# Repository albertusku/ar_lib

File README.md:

# AR_LIB

Not all the soft is tested and the 99% of the libs I have made are dependent of other libs so you must need to check if you have the other libs

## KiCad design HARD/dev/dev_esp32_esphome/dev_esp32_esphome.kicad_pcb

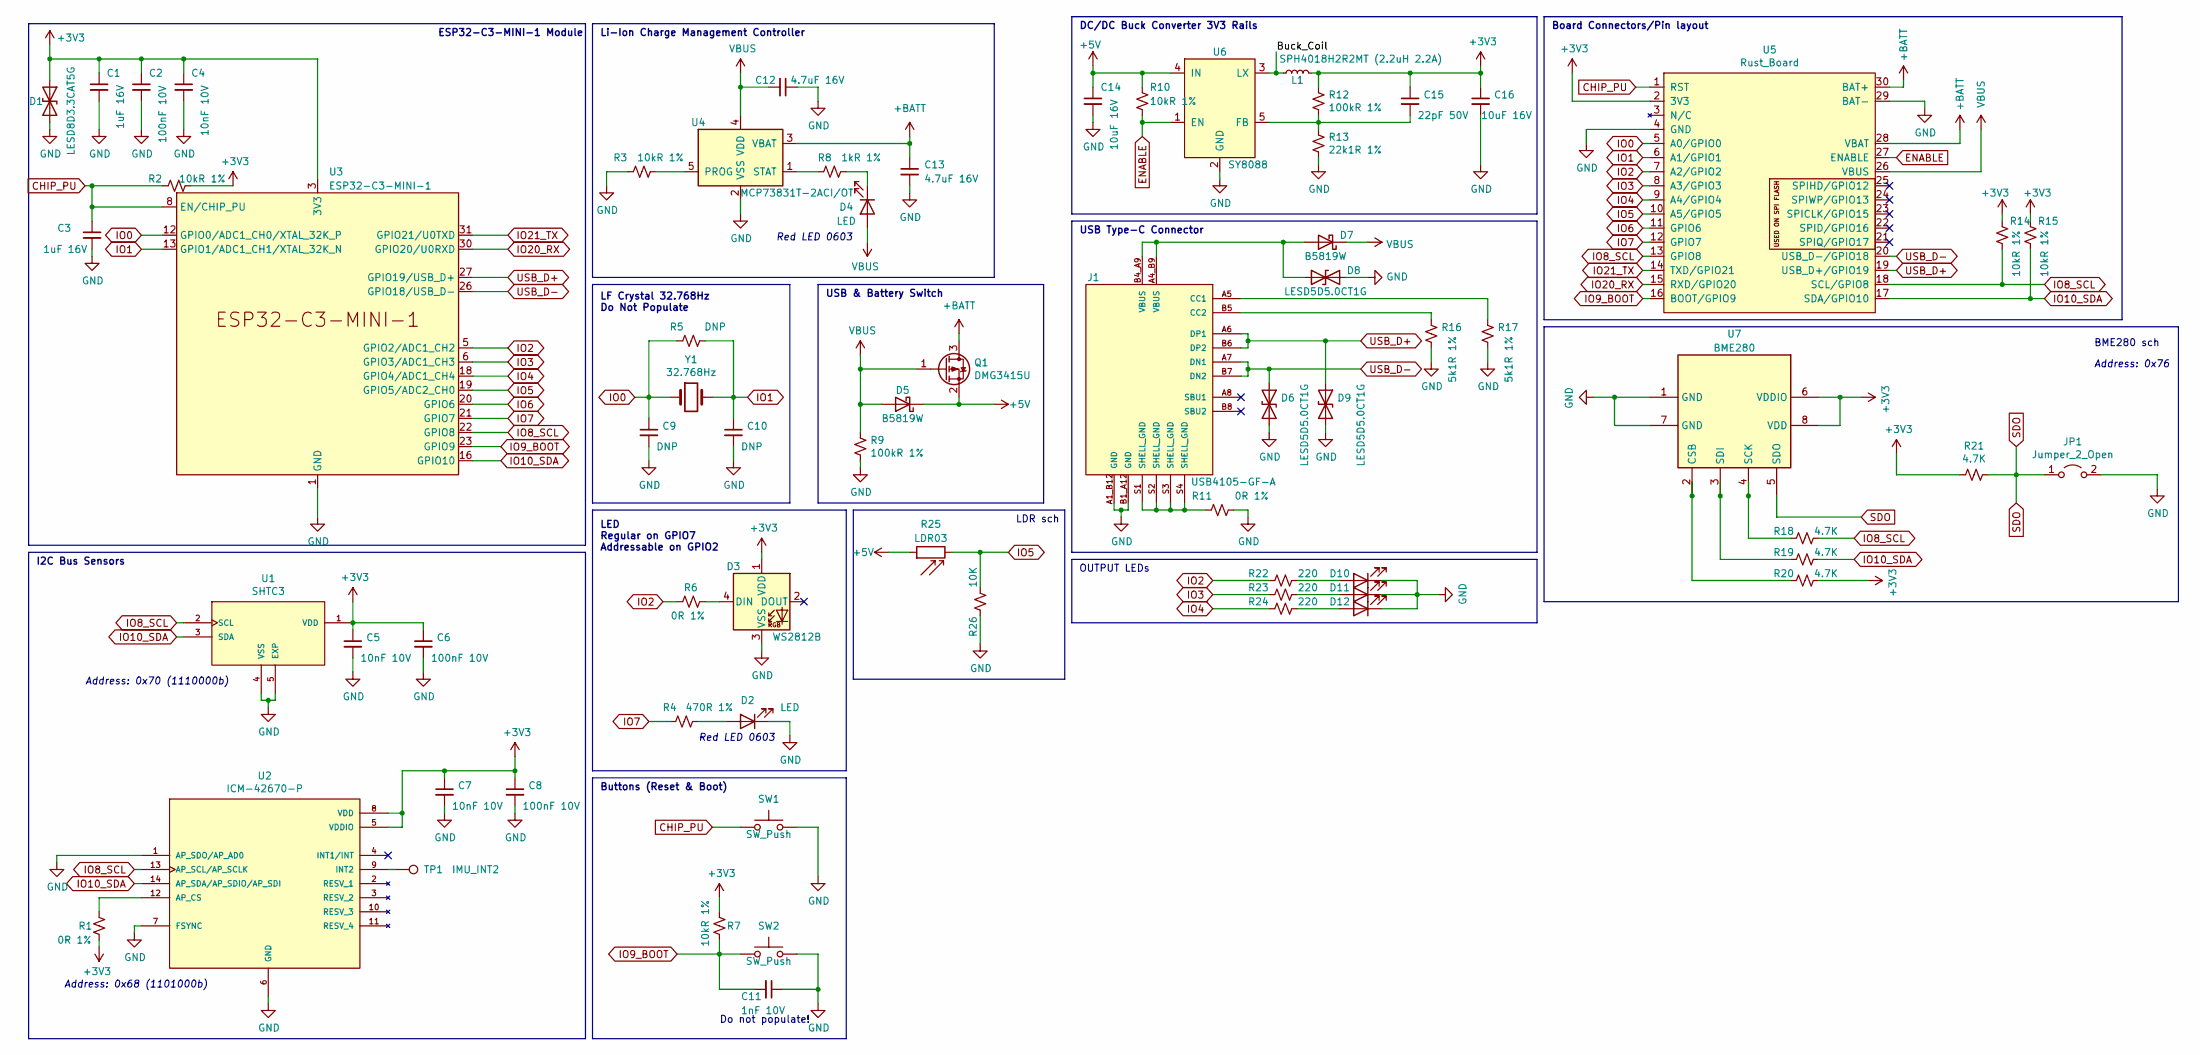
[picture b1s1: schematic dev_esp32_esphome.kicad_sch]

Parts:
C1, C3: 1uF 16V; C_0402_1005Metric; LCSC C52923
C2, C6, C8: 100nF 10V; C_0402_1005Metric; LCSC C1525
C4, C5, C7: 10nF 10V; C_0402_1005Metric; LCSC C15195
C9, C10: DNP; C_0402_1005Metric
C11: 1nF 10V; C_0402_1005Metric; LCSC C1523
C12, C13: 4.7uF 16V; C_0603_1608Metric; LCSC C19666
C14, C16: 10uF 16V; C_0805_2012Metric; LCSC C15850
C15: 22pF 50V; C_0603_1608Metric; LCSC C1653
D1: LESD8D3.3CAT5G; SOD-882; LCSC C172409
D2, D4, D10, D11, D12: LED; LED_0603_1608Metric; LCSC C2286
D3: WS2812B; LED_SK6812MINI_PLCC4_3.5x3.5mm_P1.75mm; LCSC C527089
D5, D7: B5819W; D_SOD-123; LCSC C8598
D6, D8, D9: LESD5D5.0CT1G; D_SOD-523; LCSC C383211
J1: USB4105-GF-A; GCT_USB4105-GF-A; PARTREV A3; LCSC C165948
JP1: Jumper_2_Open; SolderJumper-2_P1.3mm_Open_TrianglePad1.0x1.5mm
L1: SPH4018H2R2MT (2.2uH 2.2A); L_Bourns-SRN4018; LCSC C370436
Q1: DMG3415U; SOT-23; LCSC C96616
R1, R6, R11: 0R 1%; R_0402_1005Metric; LCSC C17168
R2, R3, R7, R10, R14, R15: 10kR 1%; R_0402_1005Metric; LCSC C25744
R4: 470R 1%; R_0402_1005Metric; LCSC C25117
R5: DNP; R_0402_1005Metric
R8: 1kR 1%; R_0402_1005Metric; LCSC C11702
R9, R12: 100kR 1%; R_0402_1005Metric; LCSC C25741
R13: 22k1R 1%; R_0402_1005Metric; LCSC C43473
R16, R17: 5k1R 1%; R_0402_1005Metric; LCSC C25905
R18, R19, R20, R21: 4.7K; R_0805_2012Metric
R22, R23, R24: 220; R_0402_1005Metric; LCSC C17168
R25: LDR03; R_LDR_10x8.5mm_P7.6mm_Vertical
R26: 10K; R_0402_1005Metric; LCSC C25117
SW1, SW2: SW_Push; SW_SPST_PTS810; LCSC C116501
TP1: IMU_INT2; TestPoint_Pad_D1.0mm
U1: SHTC3; SON100P200X200X80-5N; PARTREV 3; LCSC C194656
U2: ICM-42670-P; IC_ICM-42670-P; PARTREV 1.0
U3: ESP32-C3-MINI-1
U4: MCP73831T-2ACI/OT; SOT-23-5; LCSC C424093
U5: Rust_Board
U6: SY8088; SOT-23-5; LCSC C479072
U7: BME280; Bosch_LGA-8_2.5x2.5mm_P0.65mm_ClockwisePinNumbering
Y1: 32.768Hz; Crystal_SMD_3215-2Pin_3.2x1.5mm

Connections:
+3V3: C1.1, C2.1, C4.1, C5.1, C6.1, C7.1, C8.1, C15.1, C16.1, D1.1 (A1), D3.1 (VDD), L1.2, R1.2, R2.2, R7.1, R12.1, R14.1, R15.1, R20.1, R21.2, U1.1 (VDD), U2.5 (VDDIO), U2.8 (VDD), U3.3 (3V3), U5.2 (3V3), U7.6 (VDDIO), U7.8 (VDD)
+5V: C14.1, D5.1 (K), Q1.2 (S), R10.1, R25.1, U6.4 (IN)
+BATT: C13.1, Q1.3 (D), U4.3 (VBAT), U5.28 (VBAT), U5.30 (BAT+)
/Buck_Coil: L1.1, U6.3 (LX)
CHIP_PU: C3.1, R2.1, SW1.1, U3.8 (EN/CHIP_PU), U5.1 (RST)
ENABLE: R10.2, U5.27 (ENABLE), U6.1 (EN)
GND: C1.2, C2.2, C3.2, C4.2, C5.2, C6.2, C7.2, C8.2, C9.2, C10.2, C11.1, C12.1, C13.2, C14.2, C16.2, D1.2 (A2), D2.1 (K), D3.3 (VSS), D6.2 (A2), D8.2 (A2), D9.2 (A2), D10.1 (K), D11.1 (K), D12.1 (K), J1.A1_B12 (GND), J1.B1_A12 (GND), JP1.2 (B), R3.1, R9.2, R11.2, R13.2, R16.2, R17.2, R26.1, SW1.2, SW2.2, U1.4 (VSS), U1.5 (EXP), U2.1 (AP_SDO/AP_AD0), U2.6 (GND), U2.7 (FSYNC), U3.1 (GND), U3.2 (GND), U3.11 (GND), U3.14 (GND), U3.36 (GND), U3.37 (GND), U3.38 (GND), U3.39 (GND), U3.40 (GND), U3.41 (GND), U3.42 (GND), U3.43 (GND), U3.44 (GND), U3.45 (GND), U3.46 (GND), U3.47 (GND), U3.48 (GND), U3.49 (GND), U3.50 (GND), U3.51 (GND), U3.52 (GND), U3.53 (GND), U4.2 (VSS), U5.4 (GND), U5.29 (BAT-), U6.2 (GND), U7.1 (GND), U7.7 (GND)
IO0: C9.1, R5.1, U3.12 (GPIO0/ADC1_CH0/XTAL_32K_P), U5.5 (A0/GPIO0), Y1.1
IO1: C10.1, R5.2, U3.13 (GPIO1/ADC1_CH1/XTAL_32K_N), U5.6 (A1/GPIO1), Y1.2
IO2: R6.1, R22.1, U3.5 (GPIO2/ADC1_CH2), U5.7 (A2/GPIO2)
IO3: R23.1, U3.6 (GPIO3/ADC1_CH3), U5.8 (A3/GPIO3)
IO4: R24.1, U3.18 (GPIO4/ADC1_CH4), U5.9 (A4/GPIO4)
IO5: R25.2, R26.2, U3.19 (GPIO5/ADC2_CH0), U5.10 (A5/GPIO5)
IO6: U3.20 (GPIO6), U5.11 (GPIO6)
IO7: R4.1, U3.21 (GPIO7), U5.12 (GPIO7)
IO8_SCL: R14.2, R18.1, U1.2 (SCL), U2.13 (AP_SCL/AP_SCLK), U3.22 (GPIO8), U5.13 (GPIO8), U5.18 (SCL/GPIO8)
IO9_BOOT: C11.2, R7.2, SW2.1, U3.23 (GPIO9), U5.16 (BOOT/GPIO9)
IO10_SDA: R15.2, R19.1, U1.3 (SDA), U2.14 (AP_SDA/AP_SDIO/AP_SDI), U3.16 (GPIO10), U5.17 (SDA/GPIO10)
IO20_RX: U3.30 (GPIO20/U0RXD), U5.15 (RXD/GPIO20)
IO21_TX: U3.31 (GPIO21/U0TXD), U5.14 (TXD/GPIO21)
unnamed: D2.2 (A), R4.2
unnamed: D3.4 (DIN), R6.2
unnamed: D4.1 (K), R8.2
unnamed: D7.2 (A), D8.1 (A1), J1.A4_B9 (VBUS), J1.B4_A9 (VBUS)
unnamed: D10.2 (A), R22.2
unnamed: D11.2 (A), R23.2
unnamed: D12.2 (A), R24.2
unnamed: J1.A5 (CC1), R17.1
unnamed: J1.B5 (CC2), R16.1
unnamed: J1.S1 (SHELL_GND), J1.S2 (SHELL_GND), J1.S3 (SHELL_GND), J1.S4 (SHELL_GND), R11.1
unnamed: R1.1, U2.12 (AP_CS)
unnamed: TP1.1, U2.9 (INT2)
unnamed: R3.2, U4.5 (PROG)
unnamed: R8.1, U4.1 (STAT)
unnamed: C15.2, R12.2, R13.1, U6.5 (FB)
unnamed: R20.2, U7.2 (CSB)
unnamed: R18.2, U7.4 (SCK)
unnamed: R19.2, U7.3 (SDI)
SDO: JP1.1 (A), R21.1, U7.5 (SDO)
USB_D+: D9.1 (A1), J1.A6 (DP1), J1.B6 (DP2), U3.27 (GPIO19/USB_D+), U5.19 (USB_D+/GPIO19)
USB_D-: D6.1 (A1), J1.A7 (DN1), J1.B7 (DN2), U3.26 (GPIO18/USB_D-), U5.20 (USB_D-/GPIO18)
VBUS: C12.2, D4.2 (A), D5.2 (A), D7.1 (K), Q1.1 (G), R9.1, U4.4 (VDD), U5.26 (VBUS)

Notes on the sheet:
Board Connectors/Pin layout
BME280 sch
Address: 0x68 (1101000b)
OUTPUT LEDs
I2C Bus Sensors
LED Regular on GPIO7 Addressable on GPIO2
Red LED 0603
LDR sch
Buttons (Reset & Boot)
USB & Battery Switch
LF Crystal 32.768Hz Do Not Populate
USB Type-C Connector
Address: 0x76
Li-Ion Charge Management Controller
DC/DC Buck Converter 3V3 Rails
ESP32-C3-MINI-1 Module
Do not populate!
Address: 0x70 (1110000b)

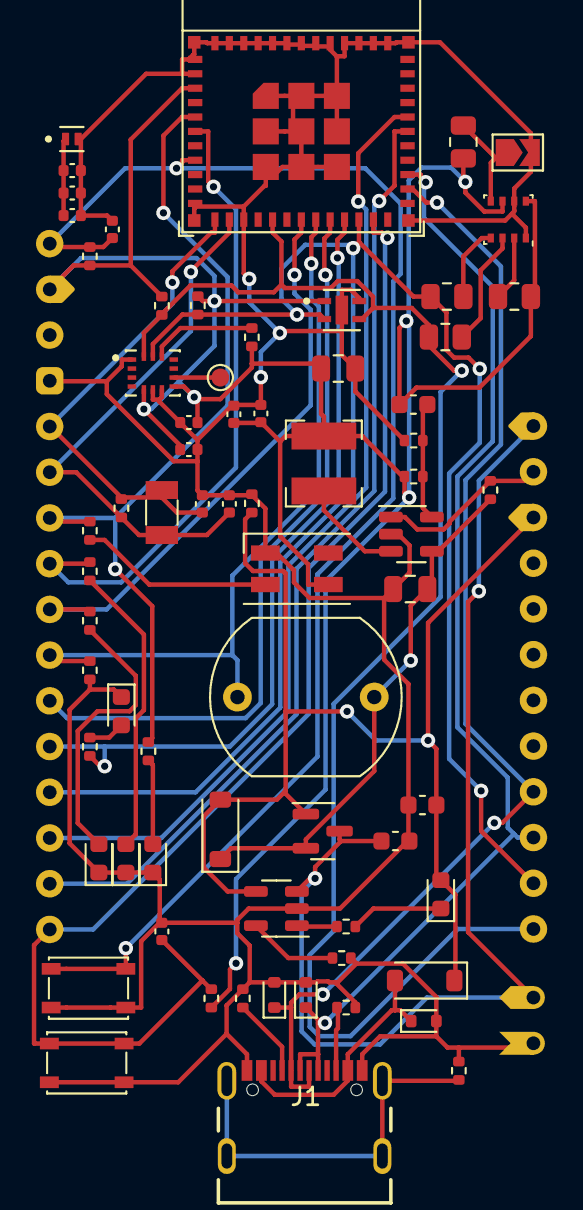
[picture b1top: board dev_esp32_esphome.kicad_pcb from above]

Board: 2 copper layers, 69 parts (0 on the bottom side), 42 nets.

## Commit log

2024-04-20 Some libs, no checked
2024-04-20 gitignore
2024-04-20 Test gitignore and security changes
2024-04-20 To delete in remote
2024-04-20 Mod .igno
2024-04-20 Serial_com
2024-04-20 Update WLAN_LIB.cpp
    Deleted global var
2024-04-20 Finish at 20/04/2024
2024-04-22 update gitignore because of HARD
2024-04-22 join of bme280 and esp32 with leds
2024-04-23 Creating submodules 1/2
2024-04-23 Creating submodules 2/2
2024-04-23 Colocation of componentes, no enroute
2024-05-01 With route
